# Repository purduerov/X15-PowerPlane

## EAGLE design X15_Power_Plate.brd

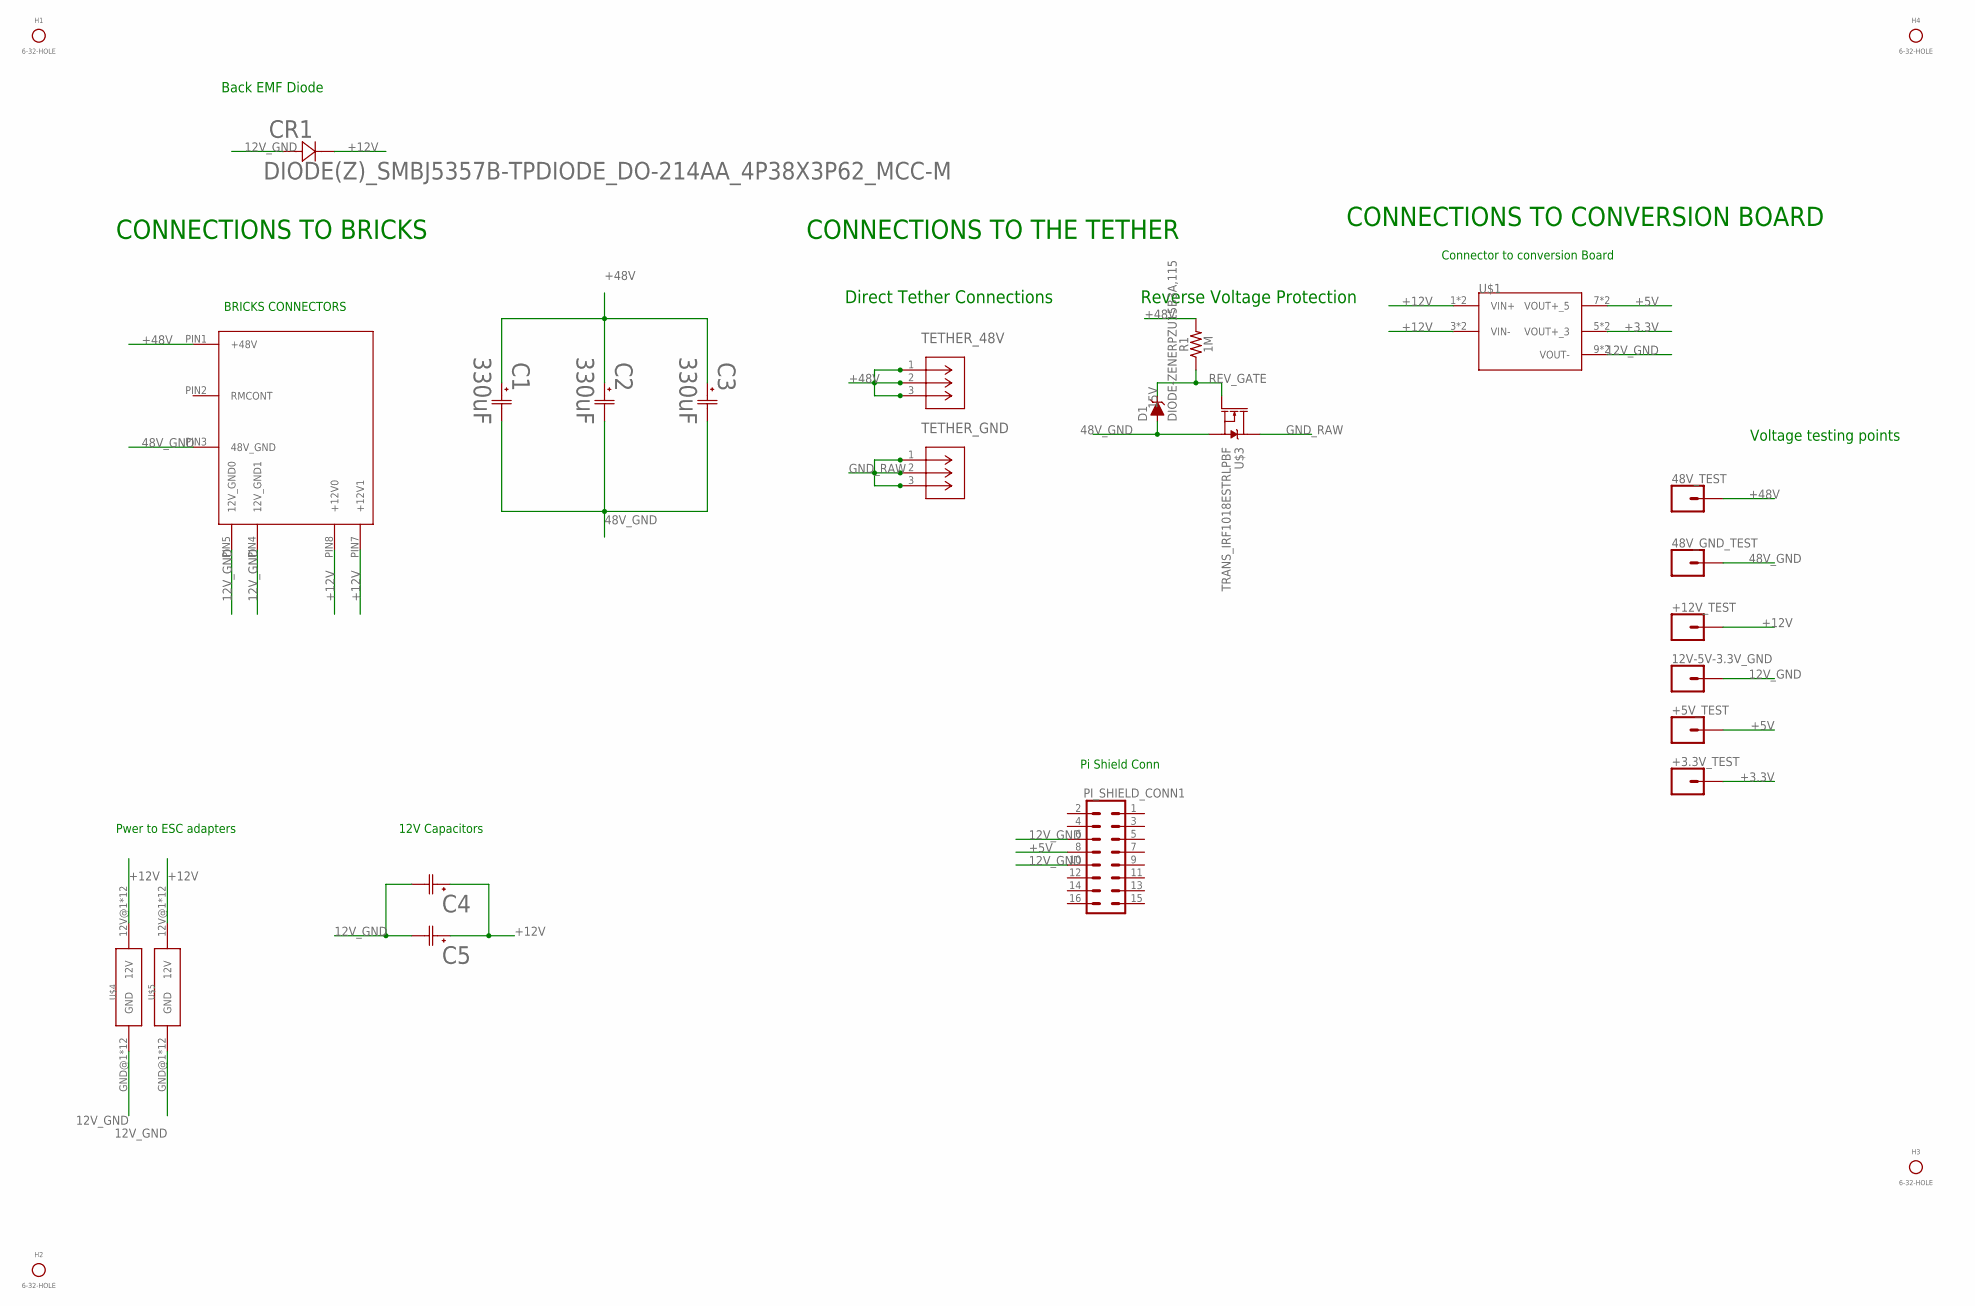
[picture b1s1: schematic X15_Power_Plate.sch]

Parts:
12V-5V-3.3V_GND, 48V_GND_TEST, 48V_TEST: CONN_01; 1X01
+3.3V_TEST, +5V_TEST, +12V_TEST: CONN_01; 1X01
C1, C2, C3: 330uF; CAP_099112E3_VIS-M
C4, C5: UCV1E561MNL1GSCAP_UCD_8X10_NCH; CAP_UCD_8X10_NCH
CR1: DIODE(Z)_SMBJ5357B-TPDIODE_DO-214AA_4P38X3P62_MCC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; DIODE_DO-214AA_4P38X3P62_MCC-M
D1: DIODE-ZENERPZU15B3A,115; SOD-323
H1, H2, H3, H4: 6-32-HOLE
PI_SHIELD_CONN1: 8X_CONN; IPL7X2
R1: 1M; 0603
TETHER_48V: 796636-3(TETHER); CON3_P5MM_VER_TERM-BLK_TYC
TETHER_GND: 796636-3(TETHER); CON3_P5MM_VER_TERM-BLK_TYC
U$1: CONN_DISTRIBUTION_TO_CONVERSION; TSW-105-05-G-S(D-C)
U$2: CONN_BMR480_CONNECTOR; BMR480_CONNECTOR
U$3: TRANS_IRF1018ESTRLPBF; D2PAK
U$4, U$5: BACKPLANE_ESC_ADAPTER_PWRBKP; BACKPLANE_ESC_ADAPTER_BKP_PWR

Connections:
12V_GND: 12V-5V-3.3V_GND.1, C4.2, C5.2, CR1.2, PI_SHIELD_CONN1.6 (17), PI_SHIELD_CONN1.10 (21), U$1.9 (VOUT-), U$1.10 (VOUT-), U$2.PIN4 (12V_GND1), U$2.PIN5 (12V_GND0), U$4.GND@1 (GND), U$4.GND@2 (GND), U$4.GND@3 (GND), U$4.GND@4 (GND), U$4.GND@5 (GND), U$4.GND@6 (GND), U$4.GND@7 (GND), U$4.GND@8 (GND), U$4.GND@9 (GND), U$4.GND@10 (GND), U$4.GND@11 (GND), U$4.GND@12 (GND), U$5.GND@1 (GND), U$5.GND@2 (GND), U$5.GND@3 (GND), U$5.GND@4 (GND), U$5.GND@5 (GND), U$5.GND@6 (GND), U$5.GND@7 (GND), U$5.GND@8 (GND), U$5.GND@9 (GND), U$5.GND@10 (GND), U$5.GND@11 (GND), U$5.GND@12 (GND)
48V_GND: 48V_GND_TEST.1, C1.2, C2.2, C3.2, D1.A, U$2.PIN3 (48V_GND), U$3.2 (S)
+3.3V: +3.3V_TEST.1, U$1.5 (VOUT+_3), U$1.6 (VOUT+_3)
+5V: +5V_TEST.1, PI_SHIELD_CONN1.8 (19), U$1.7 (VOUT+_5), U$1.8 (VOUT+_5)
+12V: +12V_TEST.1, C4.1, C5.1, CR1.1, U$1.1 (VIN+), U$1.2 (VIN+), U$1.3 (VIN-), U$1.4 (VIN-), U$2.PIN7 (+12V1), U$2.PIN8 (+12V0), U$4.12V@1 (12V), U$4.12V@2 (12V), U$4.12V@3 (12V), U$4.12V@4 (12V), U$4.12V@5 (12V), U$4.12V@6 (12V), U$4.12V@7 (12V), U$4.12V@8 (12V), U$4.12V@9 (12V), U$4.12V@10 (12V), U$4.12V@11 (12V), U$4.12V@12 (12V), U$5.12V@1 (12V), U$5.12V@2 (12V), U$5.12V@3 (12V), U$5.12V@4 (12V), U$5.12V@5 (12V), U$5.12V@6 (12V), U$5.12V@7 (12V), U$5.12V@8 (12V), U$5.12V@9 (12V), U$5.12V@10 (12V), U$5.12V@11 (12V), U$5.12V@12 (12V)
+48V: 48V_TEST.1, C1.1, C2.1, C3.1, R1.2, TETHER_48V.1, TETHER_48V.2, TETHER_48V.3, U$2.PIN1 (+48V)
GND_RAW: TETHER_GND.1, TETHER_GND.2, TETHER_GND.3, U$3.3 (D)
REV_GATE: D1.C, R1.1, U$3.1 (G)

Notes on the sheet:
CONNECTIONS TO BRICKS
BRICKS CONNECTORS
CONNECTIONS TO THE TETHER
Reverse Voltage Protection
Direct Tether Connections
CONNECTIONS TO CONVERSION BOARD
Connector to conversion Board
Back EMF Diode
Voltage testing points
Pwer to ESC adapters
12V Capacitors
Pi Shield Conn

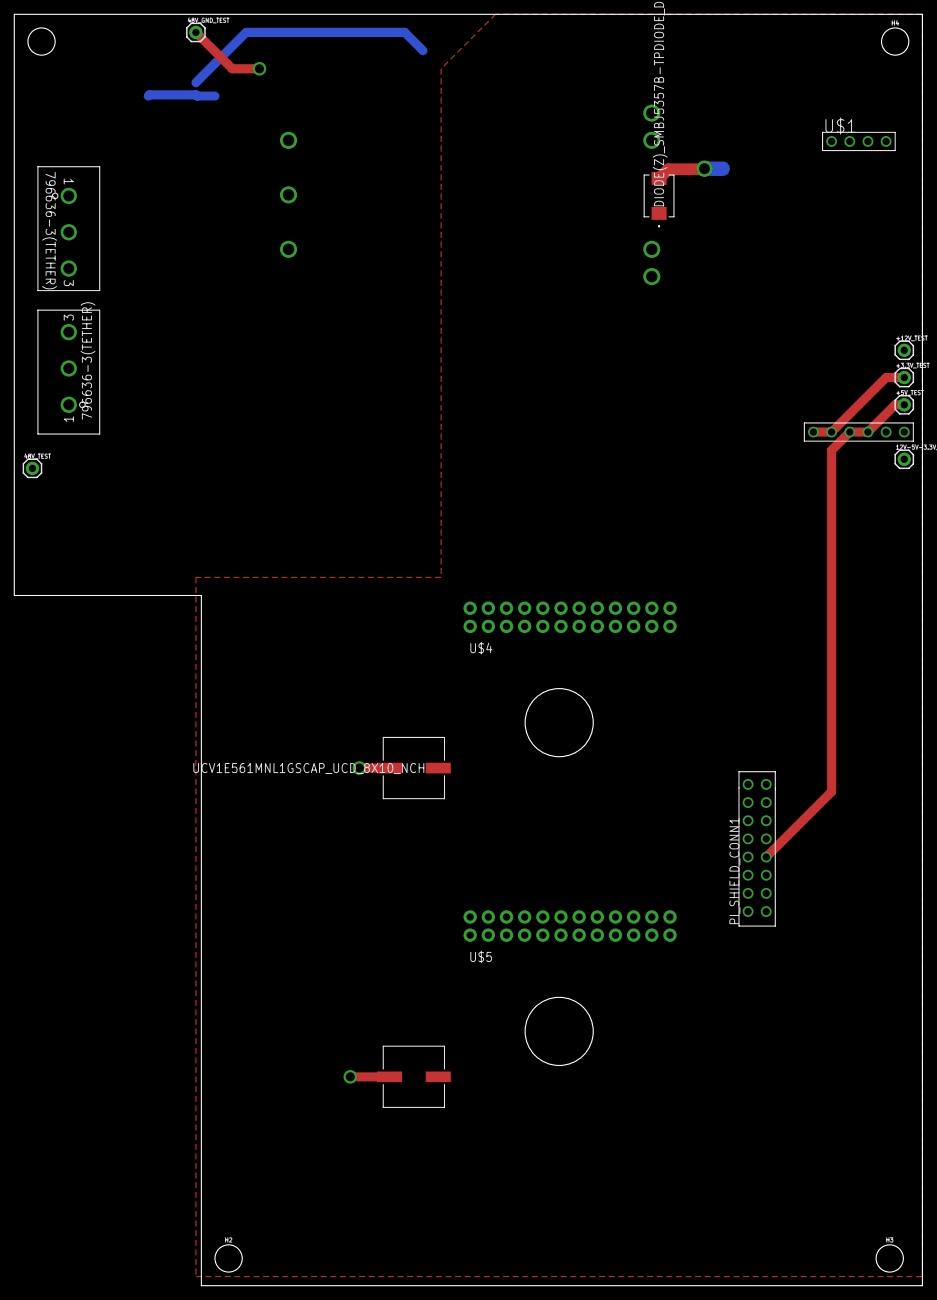
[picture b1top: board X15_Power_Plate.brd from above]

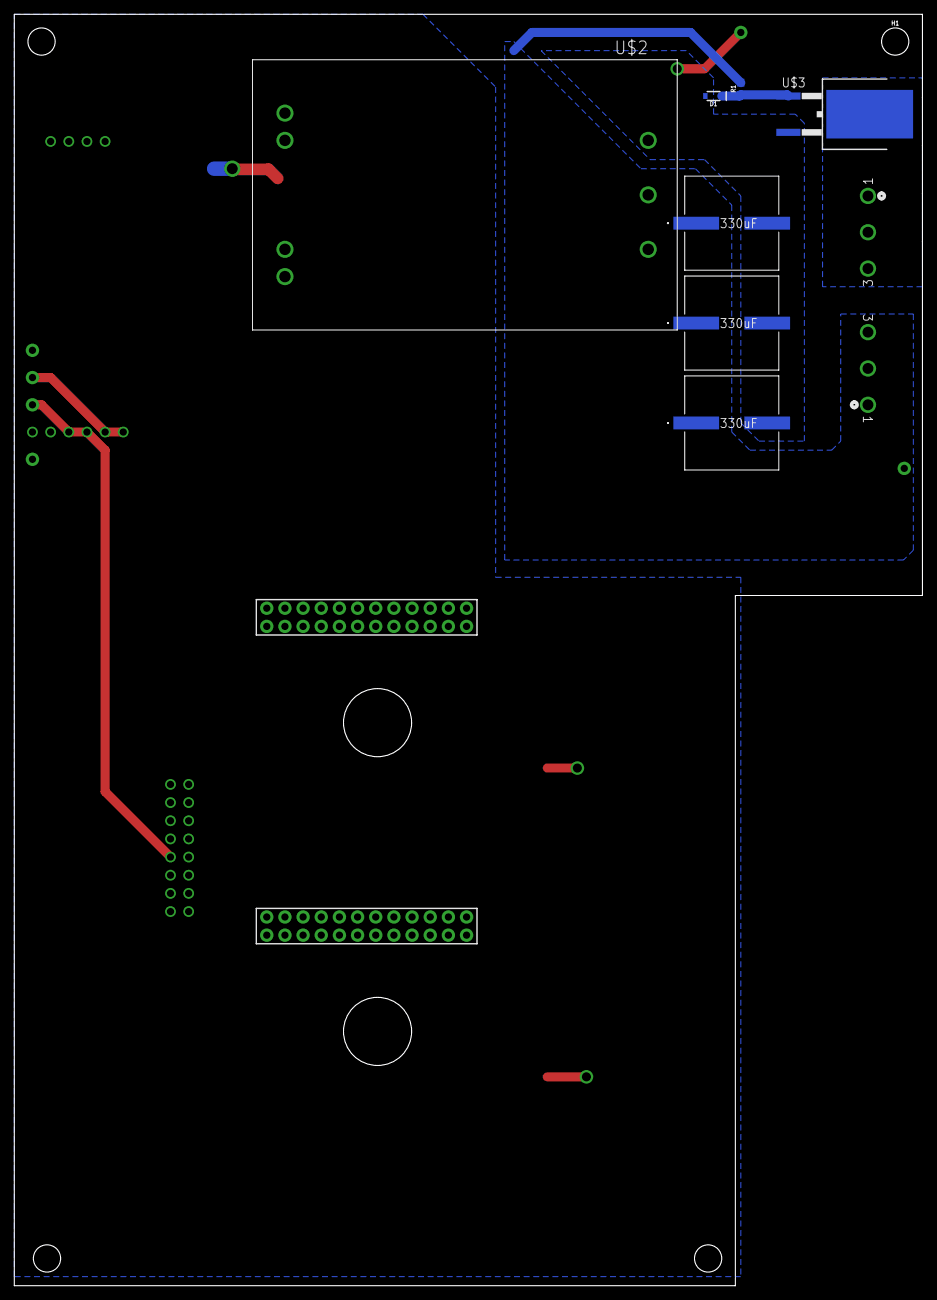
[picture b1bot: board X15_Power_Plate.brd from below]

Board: 2 copper layers, 127.0 x 177.8 mm, 26 parts (8 on the bottom side), 8 nets.

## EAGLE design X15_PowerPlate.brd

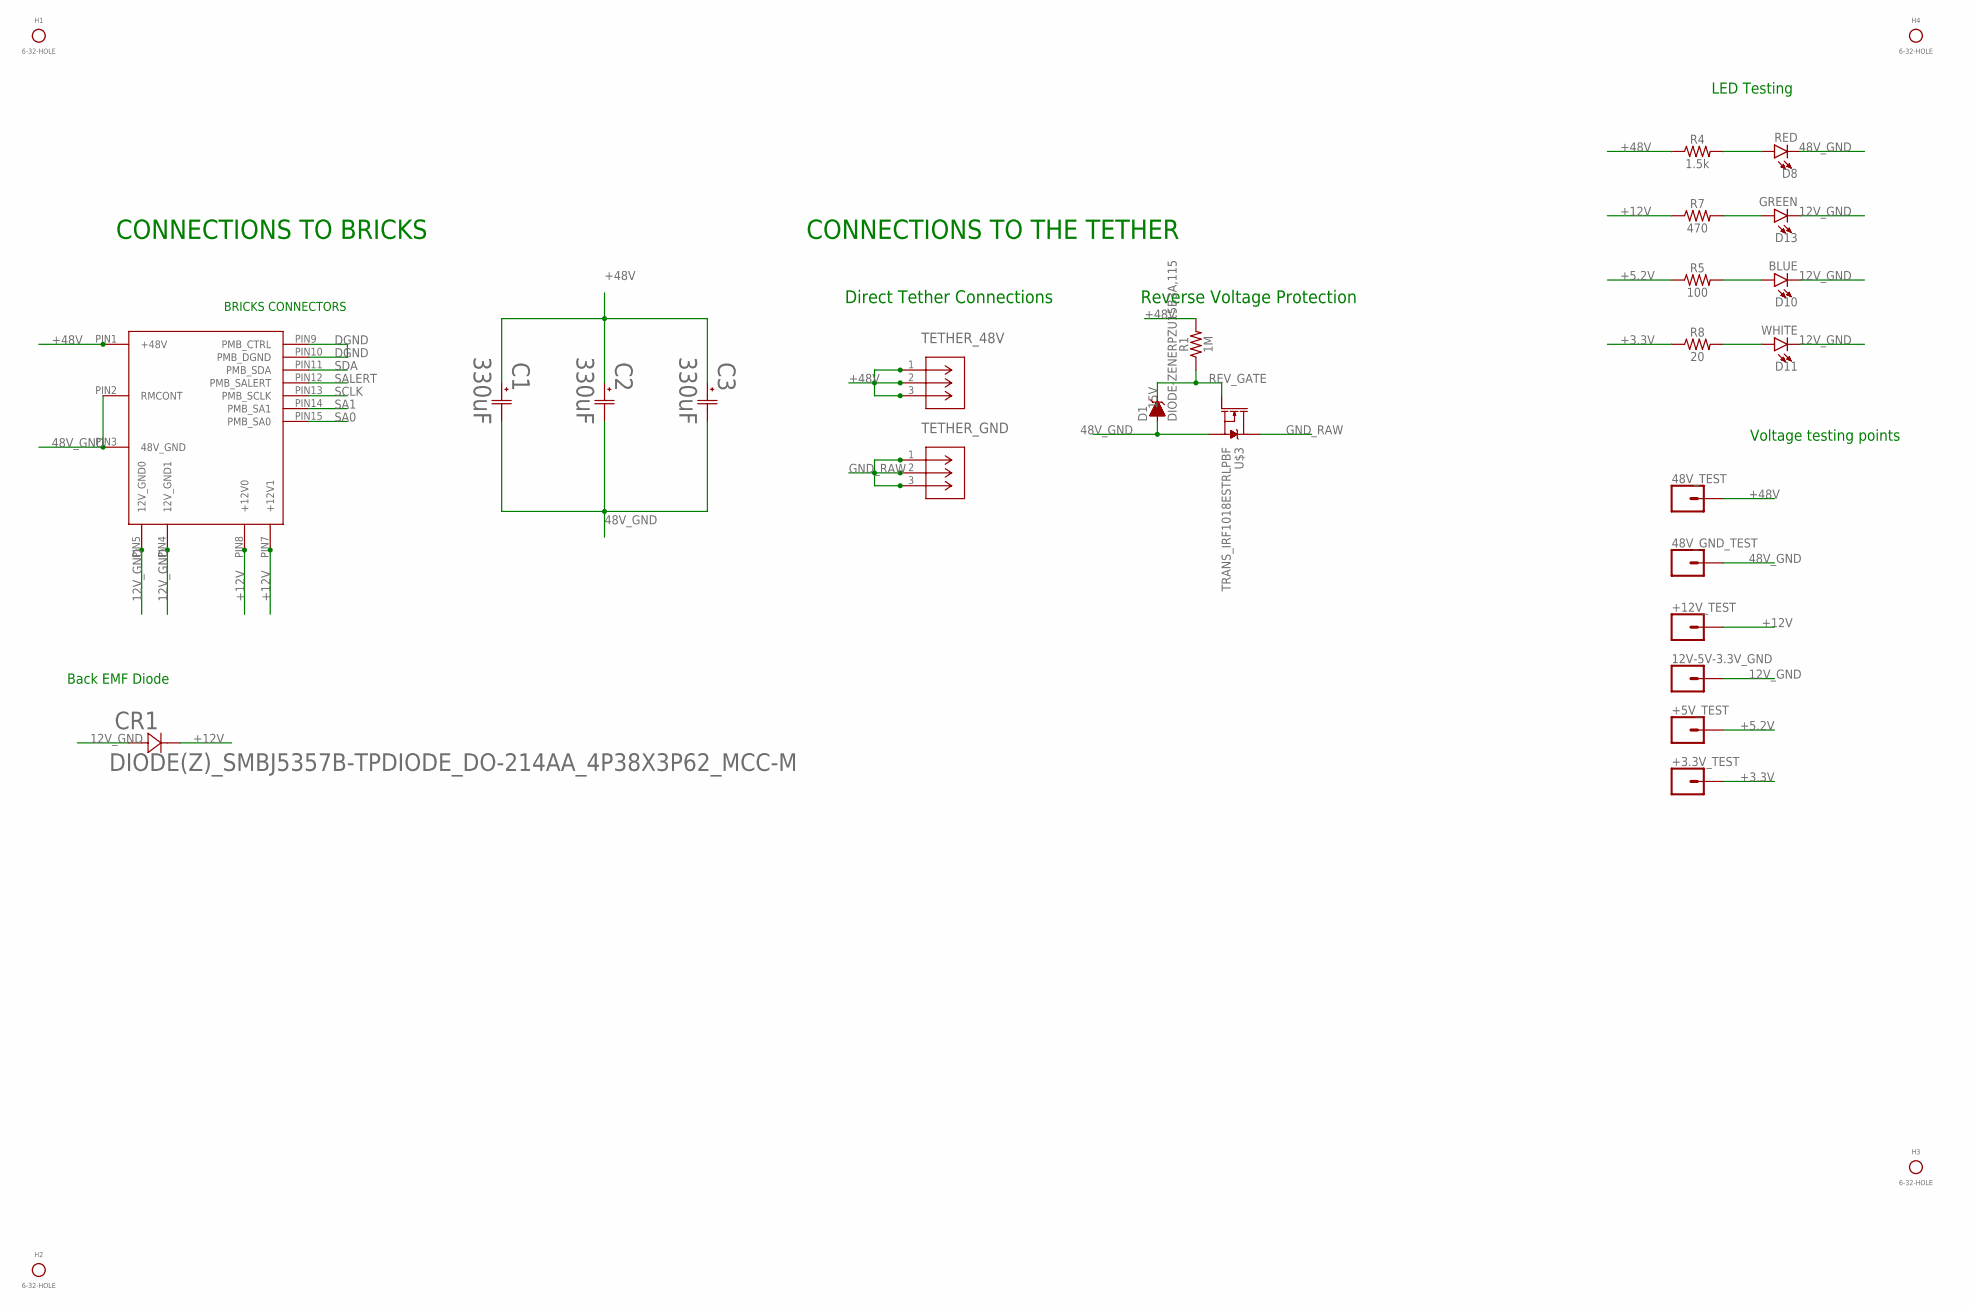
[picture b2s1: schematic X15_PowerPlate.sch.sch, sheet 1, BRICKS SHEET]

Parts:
12V-5V-3.3V_GND, 48V_GND_TEST, 48V_TEST: CONN_01; 1X01
+3.3V_TEST, +5V_TEST, +12V_TEST: CONN_01; 1X01
C1, C2, C3: 330uF; CAP_099112E3_VIS-M
CR1: DIODE(Z)_SMBJ5357B-TPDIODE_DO-214AA_4P38X3P62_MCC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; DIODE_DO-214AA_4P38X3P62_MCC-M
D1: DIODE-ZENERPZU15B3A,115; SOD-323
D8: RED; LED-0603
D10: BLUE; LED-0603
D11: WHITE; LED-0603
D13: GREEN; LED-0603
H1, H2, H3, H4: 6-32-HOLE
R1: 1M; 0603
R4: 1.5k; 0603
R5: 100; 0603
R7: 470; 0603
R8: 20; 0603
TETHER_48V: 796636-3(TETHER); CON3_P5MM_VER_TERM-BLK_TYC
TETHER_GND: 796636-3(TETHER); CON3_P5MM_VER_TERM-BLK_TYC
U$2: CONN_BMR480_CONNECTOR(BRICK); BMR480_CONNECTOR
U$3: TRANS_IRF1018ESTRLPBF; D2PAK

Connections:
12V_GND: 12V-5V-3.3V_GND.1, CR1.2, D10.C, D11.C, D13.C, U$2.PIN4 (12V_GND1), U$2.PIN5 (12V_GND0); also elsewhere on the board
48V_GND: 48V_GND_TEST.1, C1.2, C2.2, C3.2, D1.A, D8.C, U$2.PIN2 (RMCONT), U$2.PIN3 (48V_GND), U$3.2 (S)
+3.3V: +3.3V_TEST.1, R8.1; also elsewhere on the board
+5.2V: +5V_TEST.1, R5.1; also elsewhere on the board
+12V: +12V_TEST.1, CR1.1, R7.1, U$2.PIN7 (+12V1), U$2.PIN8 (+12V0); also elsewhere on the board
+48V: 48V_TEST.1, C1.1, C2.1, C3.1, R1.2, R4.1, TETHER_48V.1, TETHER_48V.2, TETHER_48V.3, U$2.PIN1 (+48V)
DGND: U$2.PIN9 (PMB_CTRL), U$2.PIN10 (PMB_DGND)
GND_RAW: TETHER_GND.1, TETHER_GND.2, TETHER_GND.3, U$3.3 (D)
unnamed: D8.A, R4.2
unnamed: D10.A, R5.2
unnamed: D11.A, R8.2
unnamed: D13.A, R7.2
REV_GATE: D1.C, R1.1, U$3.1 (G)
SA0: U$2.PIN15 (PMB_SA0)
SA1: U$2.PIN14 (PMB_SA1)
SALERT: U$2.PIN12 (PMB_SALERT)
SCLK: U$2.PIN13 (PMB_SCLK)
SDA: U$2.PIN11 (PMB_SDA)

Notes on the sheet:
CONNECTIONS TO BRICKS
BRICKS CONNECTORS
CONNECTIONS TO THE TETHER
Reverse Voltage Protection
Direct Tether Connections
Voltage testing points
Back EMF Diode
LED Testing

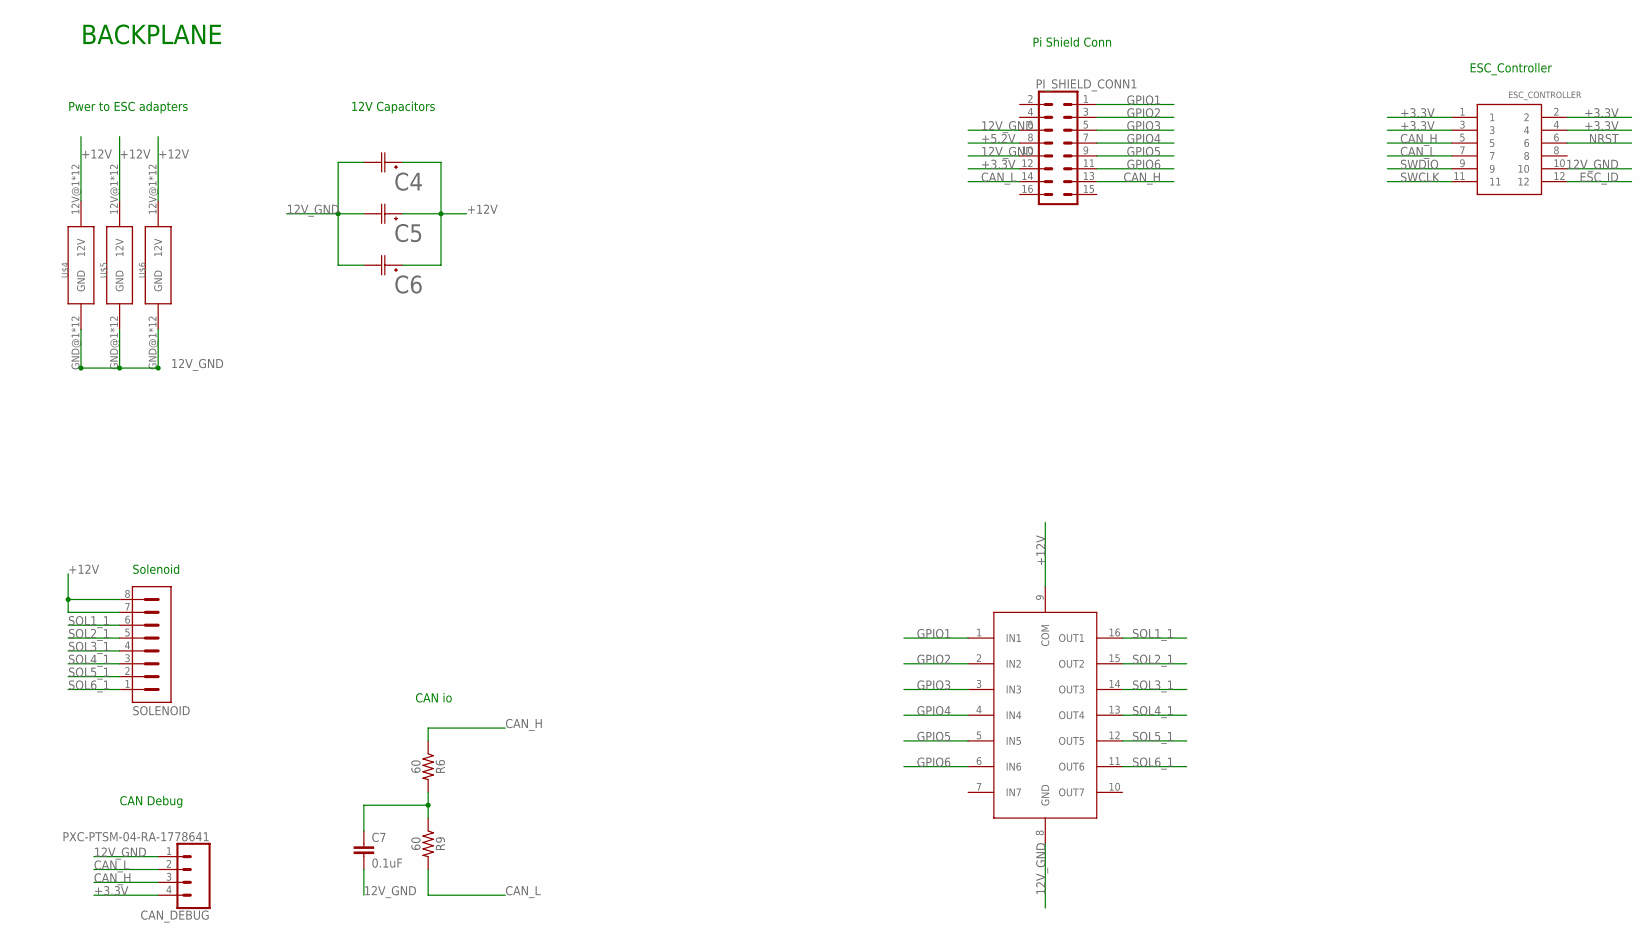
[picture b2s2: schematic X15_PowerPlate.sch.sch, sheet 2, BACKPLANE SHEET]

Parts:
C4, C5, C6: UCV1E561MNL1GSCAP_UCD_8X10_NCH; CAP_UCD_8X10_NCH
C7: 0.1uF; 0603
CAN_DEBUG: PXC-PTSM-04-RA-1778641
ESC_CONTROLLER: BACKPLANE_CONNECTORSBKP; BACKPLANE_CONNECTORS_BKP
PI_SHIELD_CONN1: 8X_CONN; IPL7X2
R6, R9: 60; 0603
SOLENOID: PXC-8-RA-1778683
U2: ULN2003AD; 16-SOIC
U$4, U$5, U$6: BACKPLANE_ESC_ADAPTER_PWRBKP; BACKPLANE_ESC_ADAPTER_BKP_PWR

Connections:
12V_GND: C4.2, C5.2, C6.2, C7.2, CAN_DEBUG.1, ESC_CONTROLLER.10, PI_SHIELD_CONN1.6 (17), PI_SHIELD_CONN1.10 (21), U2.8 (GND), U$4.GND@1 (GND), U$4.GND@2 (GND), U$4.GND@3 (GND), U$4.GND@4 (GND), U$4.GND@5 (GND), U$4.GND@6 (GND), U$4.GND@7 (GND), U$4.GND@8 (GND), U$4.GND@9 (GND), U$4.GND@10 (GND), U$4.GND@11 (GND), U$4.GND@12 (GND), U$5.GND@1 (GND), U$5.GND@2 (GND), U$5.GND@3 (GND), U$5.GND@4 (GND), U$5.GND@5 (GND), U$5.GND@6 (GND), U$5.GND@7 (GND), U$5.GND@8 (GND), U$5.GND@9 (GND), U$5.GND@10 (GND), U$5.GND@11 (GND), U$5.GND@12 (GND), U$6.GND@1 (GND), U$6.GND@2 (GND), U$6.GND@3 (GND), U$6.GND@4 (GND), U$6.GND@5 (GND), U$6.GND@6 (GND), U$6.GND@7 (GND), U$6.GND@8 (GND), U$6.GND@9 (GND), U$6.GND@10 (GND), U$6.GND@11 (GND), U$6.GND@12 (GND); also elsewhere on the board
+3.3V: CAN_DEBUG.4, ESC_CONTROLLER.1, ESC_CONTROLLER.2, ESC_CONTROLLER.3, ESC_CONTROLLER.4, PI_SHIELD_CONN1.12 (23); also elsewhere on the board
+5.2V: PI_SHIELD_CONN1.8 (19); also elsewhere on the board
+12V: C4.1, C5.1, C6.1, SOLENOID.7, SOLENOID.8, U2.9 (COM), U$4.12V@1 (12V), U$4.12V@2 (12V), U$4.12V@3 (12V), U$4.12V@4 (12V), U$4.12V@5 (12V), U$4.12V@6 (12V), U$4.12V@7 (12V), U$4.12V@8 (12V), U$4.12V@9 (12V), U$4.12V@10 (12V), U$4.12V@11 (12V), U$4.12V@12 (12V), U$5.12V@1 (12V), U$5.12V@2 (12V), U$5.12V@3 (12V), U$5.12V@4 (12V), U$5.12V@5 (12V), U$5.12V@6 (12V), U$5.12V@7 (12V), U$5.12V@8 (12V), U$5.12V@9 (12V), U$5.12V@10 (12V), U$5.12V@11 (12V), U$5.12V@12 (12V), U$6.12V@1 (12V), U$6.12V@2 (12V), U$6.12V@3 (12V), U$6.12V@4 (12V), U$6.12V@5 (12V), U$6.12V@6 (12V), U$6.12V@7 (12V), U$6.12V@8 (12V), U$6.12V@9 (12V), U$6.12V@10 (12V), U$6.12V@11 (12V), U$6.12V@12 (12V); also elsewhere on the board
CAN_H: CAN_DEBUG.3, ESC_CONTROLLER.5, PI_SHIELD_CONN1.13 (1), R6.1
CAN_L: CAN_DEBUG.2, ESC_CONTROLLER.7, PI_SHIELD_CONN1.14 (2), R9.2
ESC_ID: ESC_CONTROLLER.12
GPIO1: PI_SHIELD_CONN1.1 (14), U2.1 (IN1)
GPIO2: PI_SHIELD_CONN1.3 (16), U2.2 (IN2)
GPIO3: PI_SHIELD_CONN1.5 (18), U2.3 (IN3)
GPIO4: PI_SHIELD_CONN1.7 (20), U2.4 (IN4)
GPIO5: PI_SHIELD_CONN1.9 (22), U2.5 (IN5)
GPIO6: PI_SHIELD_CONN1.11 (24), U2.6 (IN6)
unnamed: C7.1, R6.2, R9.1
NRST: ESC_CONTROLLER.6
SOL1_1: SOLENOID.6, U2.16 (OUT1)
SOL2_1: SOLENOID.5, U2.15 (OUT2)
SOL3_1: SOLENOID.4, U2.14 (OUT3)
SOL4_1: SOLENOID.3, U2.13 (OUT4)
SOL5_1: SOLENOID.2, U2.12 (OUT5)
SOL6_1: SOLENOID.1, U2.11 (OUT6)
SWCLK: ESC_CONTROLLER.11
SWDIO: ESC_CONTROLLER.9

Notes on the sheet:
Pwer to ESC adapters
12V Capacitors
Pi Shield Conn
BACKPLANE
Solenoid
CAN io
CAN Debug
ESC_Controller

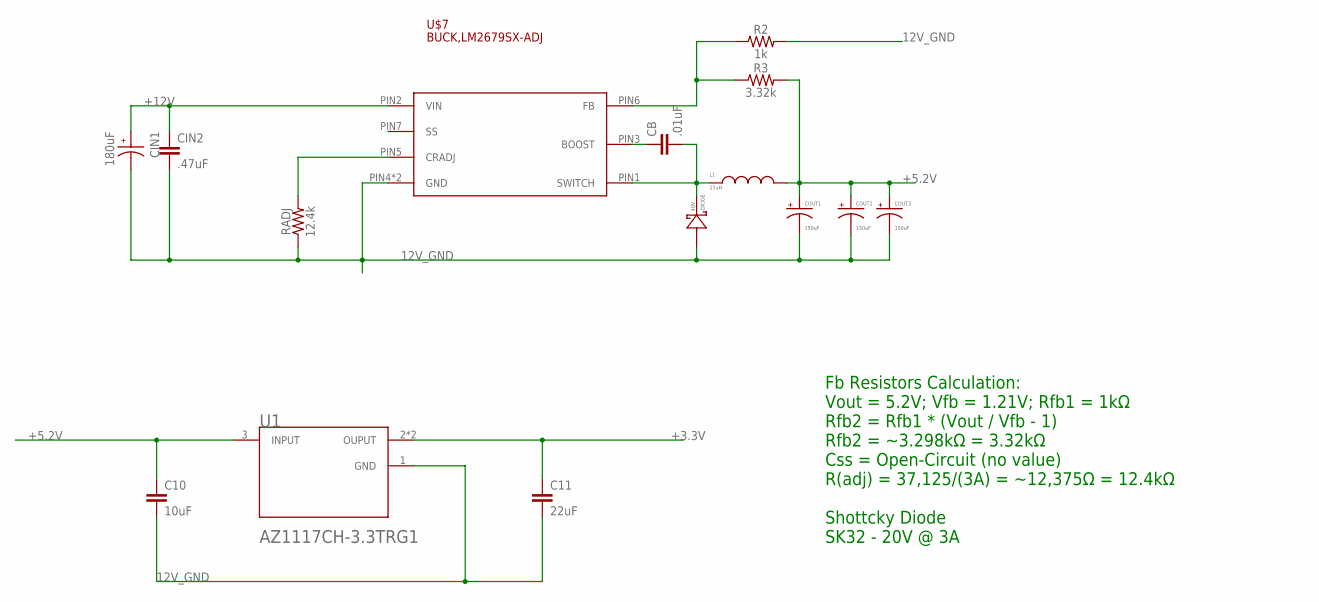
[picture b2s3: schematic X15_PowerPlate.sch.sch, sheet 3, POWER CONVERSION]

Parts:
C10: 10uF; 0603
C11: 22uF; 0603
CB: .01uF; 0603
CIN1: 180uF; CAP_EEEFKE181XSP
CIN2: .47uF; 0603
COUT1, COUT2, COUT3: 150uF; 2917(7343-31-METRIC)
DIODE: 40V; DO214AC
L1: 15uH; HCMA1305
R2: 1k; 0603
R3: 3.32k; 0603
RADJ: 12.4k; 0603
U1: LINEAR,AZ1117CR-3.3TRG1DIODES_AZ1117CH-3.3TRG1_0_0; LINEAR,AZ1117CR-3.3TRG1
U$7: BUCK,LM2679SX-ADJ

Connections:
12V_GND: C10.2, C11.2, CIN1.2, CIN2.2, COUT1.-, COUT2.-, COUT3.-, DIODE.A (2), R2.2, RADJ.1, U1.1 (GND), U$7.PIN4 (GND), U$7.PIN8 (GND); also elsewhere on the board
+3.3V: C11.1, U1.2 (OUPUT), U1.4 (OUPUT); also elsewhere on the board
+5.2V: C10.1, COUT1.+, COUT2.+, COUT3.+, L1.2, R3.2, U1.3 (INPUT); also elsewhere on the board
+12V: CIN1.1, CIN2.1, U$7.PIN2 (VIN); also elsewhere on the board
BOOST: CB.1, U$7.PIN3 (BOOST)
CRADJ: RADJ.2, U$7.PIN5 (CRADJ)
FB: R2.1, R3.1, U$7.PIN6 (FB)
SWITCH: CB.2, DIODE.C (1), L1.1, U$7.PIN1 (SWITCH)

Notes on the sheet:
Fb Resistors Calculation: Vout = 5.2V; Vfb = 1.21V; Rfb1 = 1kΩ Rfb2 = Rfb1 * (Vout / Vfb - 1) Rfb2 = ~3.298kΩ = 3.32kΩ Css = Open-Circuit (no value) R(adj) = 37,125/(3A) = ~12,375Ω = 12.4kΩ Shottcky Diode SK32 - 20V @ 3A

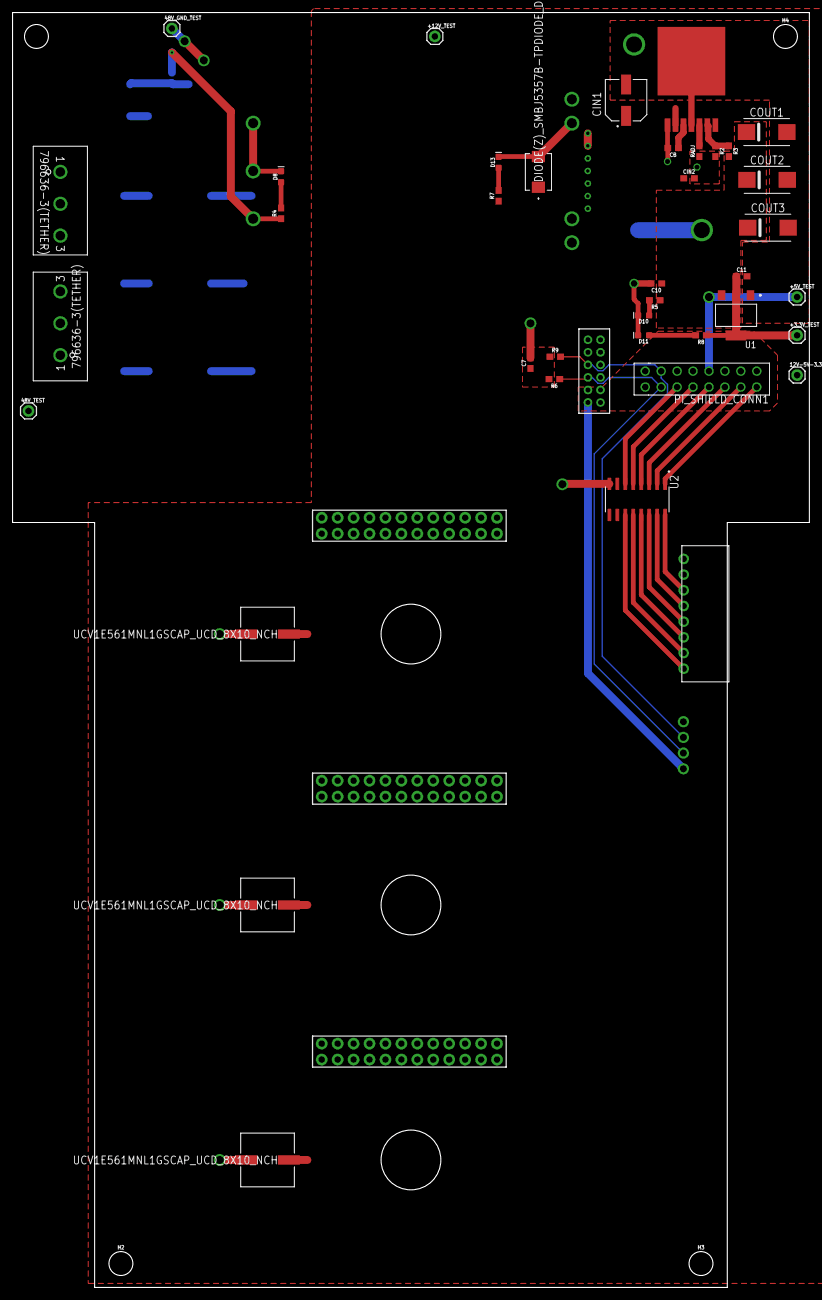
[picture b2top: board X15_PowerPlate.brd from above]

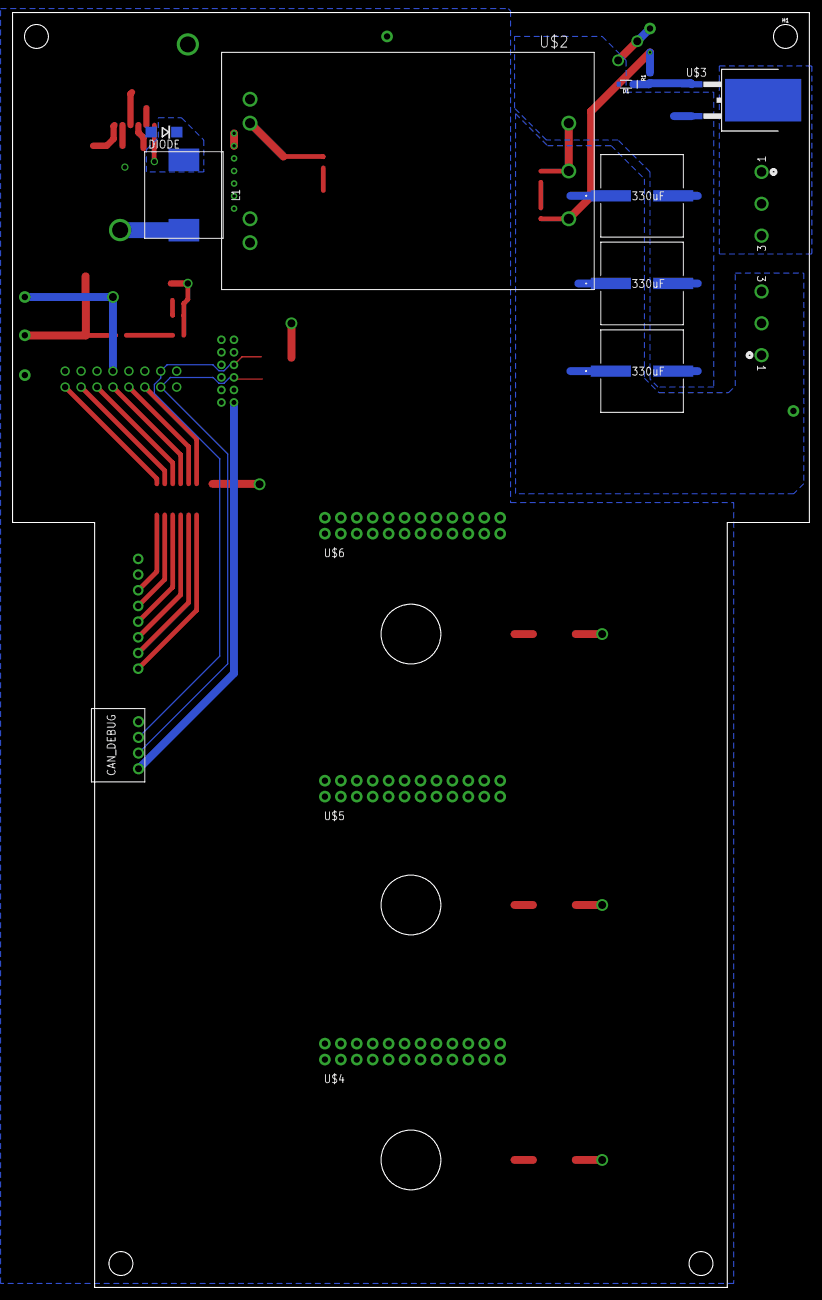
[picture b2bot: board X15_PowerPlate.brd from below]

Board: 2 copper layers, 127.0 x 203.2 mm, 57 parts (14 on the bottom side), 32 nets.

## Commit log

2023-03-30 power conversion layout finished
2023-04-03 Iteration to Simulate Current Stack

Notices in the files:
parts and their libraries:
SparkFun-DiscreteSemi: Licensing: Creative Commons ShareAlike 4.0 International - https://creativecommons.org/licenses/by-sa/4.0
COPYRIGHT: Copyright (C) 2022 Ultra Librarian. All rights reserved.
COPYRIGHT: Copyright (C) 2023 Ultra Librarian. All rights reserved.
